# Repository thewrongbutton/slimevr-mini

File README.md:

# SlimeVR Mini

Self explanatory. The official SlimeVR boards look good but there's a lot of wasted space and excess size. We can go $_{compact!}$

## Resources

#### SlimeVR
- [SlimeVR Docs](https://docs.slimevr.dev/)
- [SlimeVR Main Board (Schematics/PCB)](https://oshwlab.com/eirenliel/slimevr-imu-module)
#### ESP
- [ESP32-C3(Chip Datasheet)](https://www.espressif.com/sites/default/files/documentation/esp32-c3_datasheet_en.pdf#cd-pins-overview)
- [ESP32-C3-MINI-1(Module Datasheet)](https://www.espressif.com/sites/default/files/documentation/esp32-c3-mini-1_datasheet_en.pdf)
- [ESP32-C3-DevKitM-1(Docs/Schematics/PCB)](https://docs.espressif.com/projects/esp-idf/en/latest/esp32c3/hw-reference/esp32c3/user-guide-devkitm-1.html)
#### IMU
- [BMI160(Chip Datasheet)](https://www.bosch-sensortec.com/media/boschsensortec/downloads/datasheets/bst-bmi160-ds000.pdf)
- BMI160(Module Schematics) - (TBD separate .md with these pictures)
- [BMM150(Chip Datasheet)](https://www.bosch-sensortec.com/media/boschsensortec/downloads/datasheets/bst-bmm150-ds001.pdf)
-

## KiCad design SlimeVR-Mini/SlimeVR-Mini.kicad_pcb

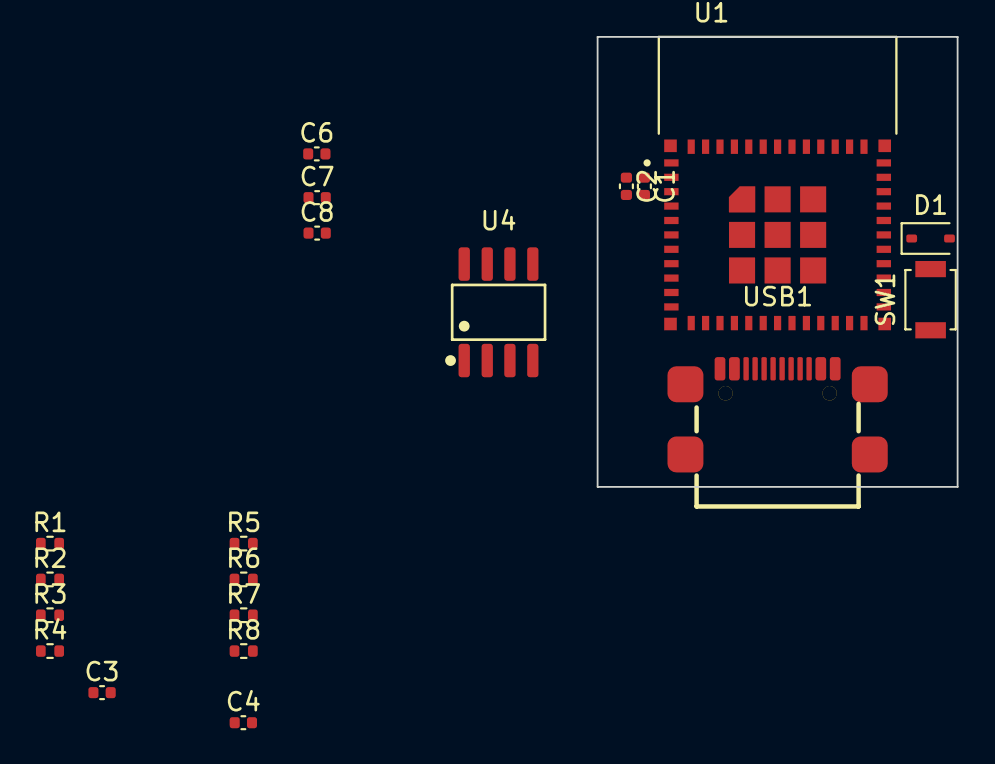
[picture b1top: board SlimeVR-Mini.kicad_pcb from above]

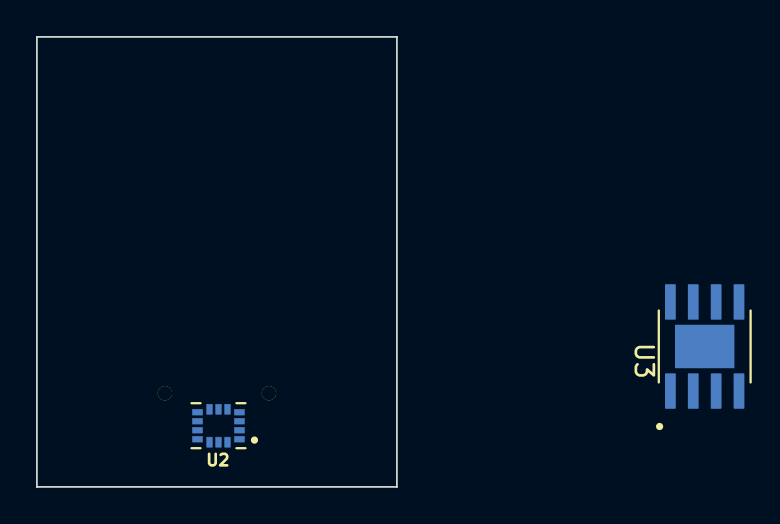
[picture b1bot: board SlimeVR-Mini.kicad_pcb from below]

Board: 2 copper layers, 20.0 x 25.0 mm, 22 parts (2 on the bottom side), 18 nets, no tracks yet.

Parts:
C1, C7: 10u; C_0402_1005Metric
C2, C4, C6, C8: 100n; C_0402_1005Metric
C3: 1u; C_0402_1005Metric
D1: 1N5819WS; D_SOD-323
R1, R3, R4: 10k; R_0402_1005Metric
R2: 40k; R_0402_1005Metric
R5, R6: 5k1; R_0402_1005Metric
R7: 1M; R_0402_1005Metric
R8: ??k; R_0402_1005Metric
SW1: SW_Push; SW_SPST_B3U-1000P
U1: ESP32-C3-MINI-1-N4
U2: BMI160; PQFN50P250X300X88-14N
U3: TP4056; SOP127P600X175-9N
U4: CH340N; SOP-8_L4.9-W3.9-P1.27-LS6.0-BL
USB1: TYPEC-304YSSW-ACP16; USB-SMD_TYPEC-304YSSW-ACP16

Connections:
+3V3: C1.2, C2.2, C4.2, R1.1, R4.1, U1.3 (3V3), U2.5 (VDDIO), U2.8 (VDD)
+BATT: R2.1, U3.5 (BAT)
/Microcontroller/BATT ADC: R2.2, R3.1, U1.5 (IO2)
/Microcontroller/BOOT: SW1.1, U1.23 (IO9)
/Microcontroller/ESP EN: C3.1, R1.2, U1.8 (EN)
/Power/D+: USB1.A6 (DP1), USB1.B6 (DP2)
/Power/D-: USB1.A7 (DN1), USB1.B7 (DN2)
GND: C1.1, C2.1, C3.2, C4.1, C6.2, C7.2, C8.2, R3.2, R5.1, R6.2, R7.1, R8.1, SW1.2, U1.1 (GND), U1.2 (GND), U1.11 (GND), U1.14 (GND), U1.36 (GND), U1.37 (GND), U1.38 (GND), U1.39 (GND), U1.40 (GND), U1.41 (GND), U1.42 (GND), U1.43 (GND), U1.44 (GND), U1.45 (GND), U1.46 (GND), U1.47 (GND), U1.48 (GND), U1.49_1 (GND), U1.49_2 (GND), U1.49_3 (GND), U1.49_4 (GND), U1.49_5 (GND), U1.49_6 (GND), U1.49_7 (GND), U1.49_8 (GND), U1.49_9 (GND), U1.50 (GND), U1.51 (GND), U1.52 (GND), U1.53 (GND), U2.6 (GNDIO), U2.7 (GND), U3.3 (GND), U4.3 (GND), USB1.A1B12 (GND), USB1.B1A12 (GND)
unnamed: R7.2, USB1.13 (GND), USB1.14 (GND), USB1.15 (GND), USB1.16 (GND)
unnamed: D1.2 (A), U4.7 (RXD)
unnamed: D1.1 (K), U1.31 (TXD0)
unnamed: R4.2, U1.22 (IO8)
unnamed: U1.30 (RXD0), U4.6 (TXD)
unnamed: R8.2, U3.2 (PROG)
unnamed: C8.1, U4.8 (V3)
unnamed: R5.2, USB1.A5 (CC1)
unnamed: R6.1, USB1.B5 (CC2)
VBUS: C6.1, C7.1, U4.5 (VCC), USB1.A4B9 (VBUS), USB1.B4A9 (VBUS)

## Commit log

2023-10-16 kicad project and libraries created
2023-10-16 added ESP32-C3-Mini-1 step model
2023-10-17 added BMI160 + prod pics and datasheets
2023-10-17 basic sheet hierarchy + schematic todo list
2023-10-17 added resource links to README
2023-10-17 converted pics to png
2023-10-17 add backup folder to .gitignore
2023-10-17 IMU wiring done-ish
2023-10-17 deleting tracked kicad backups
2023-10-18 added Power page + fixing symbols and footprints
2023-10-19 added CH340N + schematics development
2023-10-23 assigned footprints, finished USB-UART sch
2023-10-25 connected I2C lines
